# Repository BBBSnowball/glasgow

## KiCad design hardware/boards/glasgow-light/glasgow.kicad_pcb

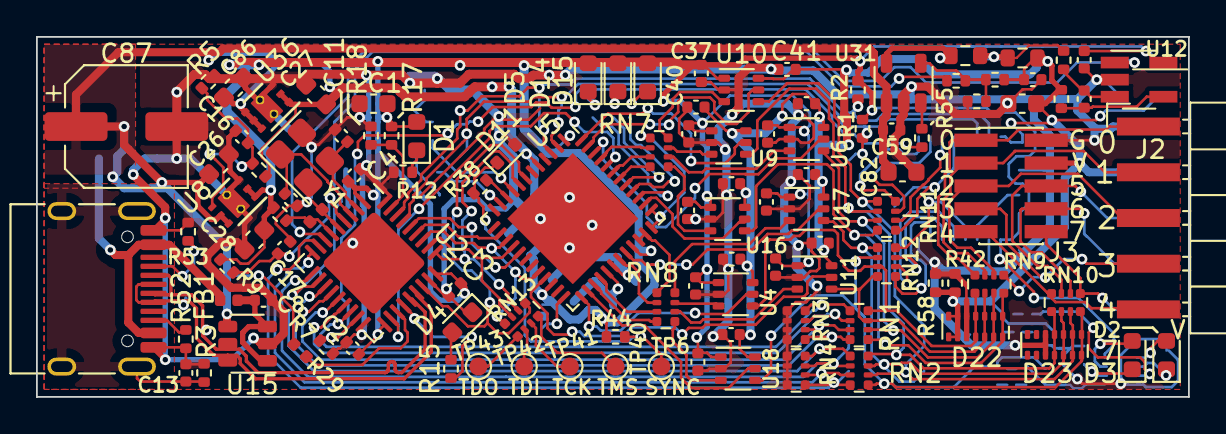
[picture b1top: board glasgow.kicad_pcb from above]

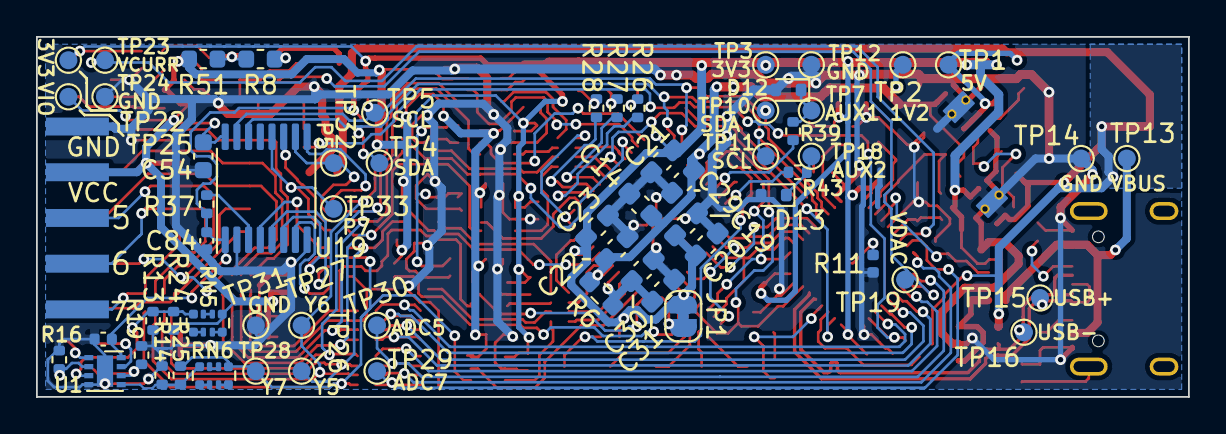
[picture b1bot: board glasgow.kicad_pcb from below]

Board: 2 copper layers, 64.0 x 20.0 mm, 173 parts (62 on the bottom side), 128 nets.

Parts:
C1, C26, C27, C28, C82, C83, C86: 4u7; C_0603_1608Metric
C2, C3, C4, C8, C13, C15, C16, C17, C32, C34, C35, C36, C37, C38, C39, C40, C41, C42, C43, C47, C48, C49, C50, C51, C52, C55, C57, C58, C59, C84: u1; C_0402_1005Metric
C11, C12: 9p; C_0402_1005Metric
C14, C19, C30: 4u7; C_0603_1608Metric_Pad1.08x0.95mm_HandSolder
C20, C21, C22, C23, C29, C31: u1; C_0603_1608Metric_Pad1.08x0.95mm_HandSolder
C54: u1; C_0603_1608Metric
C87: 150u; CP_Elec_6.3x5.9
D1: GRN; LED_0603_1608Metric
D2: GREEN; LED_0603_1608Metric
D3: YELLOW; LED_0603_1608Metric
D4, D5, D14, D15: YEL; LED_0603_1608Metric
D11, D12, D13: ESD5Z5.0T1G; D_SOD-523
D22, D23: SP3012-06UTG; UDFN-14_3.5x1.35mm_P0.5mm
FB1: 600R, 0.5A; L_0402_1005Metric
J1: USB_C_USB2.0; USB_C_Receptacle_HRO_TYPE-C-31-M-12
J2: IDC-Header_2x5_P2.54mm; PinHeader_2x05_P2.54mm_BoardEdge
J3: IDC-Header_2x5_P2.54mm; PinHeader_2x05_P1.27mm_Vertical_SMD
JP1: SolderJumper_2_Bridged; SolderJumper-2_P1.3mm_Bridged_RoundedPad1.0x1.5mm
R1, R2, R15, R42, R58: 2k2; R_0402_1005Metric
R3, R5, R18: 100k; R_0402_1005Metric
R4: 1k; R_0402_1005Metric
R6: 100; R_0603_1608Metric_Pad0.98x0.95mm_HandSolder
R7, R9, R37, R44, R55: 10k; R_0402_1005Metric
R8, R51: DNP; R_0603_1608Metric_DNP
R10, R11, R26, R27, R28, R29: 0; R_0402_1005Metric
R12: 20k; R_0402_1005Metric
R13, R14: 50k; R_0402_1005Metric
R16, R19: 270; R_0402_1005Metric
R17: DNP; R_0402_1005Metric
R24, R25: DNP/400k; R_0402_1005Metric
R30, R54: 4R7; R_0402_1005Metric
R33: 49k9; R_0402_1005Metric
R34: 59k; R_0402_1005Metric
R35: 24k3; R_0402_1005Metric
R38, R39, R43: 47R; R_0402_1005Metric
R49: 0R10; R_0603_1608Metric
R52, R53: 5k1; R_0402_1005Metric
R56: 0R68; R_0603_1608Metric
RN1, RN2, RN3, RN4, RN5, RN6: 100k; R_Array_Convex_4x0402
RN7, RN8, RN9, RN10, RN13: 33R; R_Array_Convex_4x0402
RN11, RN12: 10k; R_Array_Convex_4x0402
TP1: 5V; TestPoint_Pad_D1.0mm
TP2: 1V2; TestPoint_Pad_D1.0mm
TP3, TP22: 3V3; TestPoint_Pad_D1.0mm
TP4, TP10: SDA; TestPoint_Pad_D1.0mm
TP5, TP11: SCL; TestPoint_Pad_D1.0mm
TP6: SYNC; TestPoint_Pad_D1.0mm
TP7: AUX1; TestPoint_Pad_D1.0mm
TP12, TP24, TP31: GND; TestPoint_Pad_D1.0mm
TP13: VBUS; TestPoint_Pad_D1.0mm
TP14: USBGND; TestPoint_Pad_D1.0mm
TP15: USBDP; TestPoint_Pad_D1.0mm
TP16: USBDM; TestPoint_Pad_D1.0mm
TP18: AUX2; TestPoint_Pad_D1.0mm
TP19: VDAC; TestPoint_Pad_D1.0mm
TP23: VCURR; TestPoint_Pad_D1.0mm
TP25: VIO; TestPoint_Pad_D1.0mm
TP26: Y5; TestPoint_Pad_D1.0mm
TP27: Y6; TestPoint_Pad_D1.0mm
TP28: Y7; TestPoint_Pad_D1.0mm
TP29: ADC7; TestPoint_Pad_D1.0mm
TP30: ADC5; TestPoint_Pad_D1.0mm
TP32: P5; TestPoint_Pad_D1.0mm
TP33: P7; TestPoint_Pad_D1.0mm
TP40: TMS; TestPoint_Pad_D1.0mm
TP41: TCK; TestPoint_Pad_D1.0mm
TP42: TDI; TestPoint_Pad_D1.0mm
TP43: TDO; TestPoint_Pad_D1.0mm
U1: LM358_DFN; DFN-8-1EP_2x2mm_P0.5mm_EP1.05x1.75mm
U2: GD32VF103T; QFN-36-1EP_6x6mm_P0.5mm_EP4.1x4.1mm
U4, U6, U9, U10, U11, U16, U17, U18: SN74LVC1T45DCKR; SOT-363_SC-70-6
U5: ICE40UP5K-SG48ITR; QFN-48-1EP_7x7mm_P0.5mm_EP5.15x5.15mm
U8: TLV75533PDRVR; DFN-6-1EP_2x2mm_P0.65mm_EP1x1.6mm_ThermalVias
U12: INA180A2; SOT-23-5_HandSoldering
U15: TPD3S014; SOT-23-6
U19: PCA6408APW; TSSOP-16_4.4x5mm_P0.65mm
U31: TPS73101DBV; SOT-23-5
U36: TLV73312PQDRVR; DFN-6-1EP_2x2mm_P0.65mm_EP1x1.6mm_ThermalVias
Y1: 8M; Crystal_SMD_3225-4Pin_3.2x2.5mm

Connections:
+1V2: C14.1, C22.1, C27.1, C29.1, R4.1, R6.2, TP2.1, U5.5, U5.30, U36.1, U36.2
+3V3: C1.1, C2.1, C3.1, C4.1, C19.1, C20.1, C21.1, C23.1, C28.1, C32.1, C34.1, C35.1, C36.1, C37.1, C42.1, C43.1, C47.1, C48.1, C55.1, C84.1, D1.2, D5.2, D14.2, D15.2, JP1.1, R1.2, R2.2, R9.1, R10.2, R17.1, R37.2, R44.2, TP3.1, TP22.1, U1.8, U2.1, U2.19, U2.27, U4.1, U5.1, U5.22, U5.33, U6.1, U8.1, U8.2, U9.1, U10.1, U11.1, U12.5, U16.1, U17.1, U18.1, U19.1
+5V: C26.2, C59.1, C82.1, C86.2, C87.1, R29.1, TP1.1, U8.5, U8.6, U15.4, U31.1, U36.4, U36.5, U36.6
/AUX1: R39.2, U5.9
/AUX2: R43.2, U5.11
/BOOT0: R17.2, R18.1, U2.35
/CC1: J1.A5, R53.2
/CC2: J1.B5, R52.2
/CLKREF: U2.20, U5.44
/DA0: U4.5, U5.25
/DA1: U5.21, U11.5
/DA2: U5.46, U6.5
/DA3: U5.38, U16.5
/DA4: U5.48, U9.5
/DA5: U5.32, U17.5
/DA6: U5.47, U10.5
/DA7: U5.26, U18.5
/FPGA_DONE: RN13.1, U2.25, U5.7
/IO_Banks/AUX1~: D12.1, R39.1, TP7.1
/IO_Banks/AUX2~: D13.1, R43.1, TP18.1
/IO_Banks/IO_Buffer_A/P0: RN12.8, U19.4
/IO_Banks/IO_Buffer_A/P1: RN12.6, U19.5
/IO_Banks/IO_Buffer_A/P2: RN12.7, U19.6
/IO_Banks/IO_Buffer_A/P3: RN12.5, U19.7
/IO_Banks/IO_Buffer_A/P4: RN11.8, U19.9
/IO_Banks/IO_Buffer_A/P5: RN11.7, TP32.1, U19.10
/IO_Banks/IO_Buffer_A/P6: RN11.6, U19.11
/IO_Banks/IO_Buffer_A/P7: RN11.5, TP33.1, U19.12
/IO_Banks/IO_Buffer_A/VFB: R33.2, R34.1, R35.2, U31.4
/IO_Banks/IO_Buffer_A/VIO_EN: R55.1, U31.3
/IO_Banks/IO_Buffer_A/X0: RN7.8, U10.3
/IO_Banks/IO_Buffer_A/Y0: D22.4, D22.11, RN1.4, RN9.1, RN12.3, U4.4
/IO_Banks/IO_Buffer_A/Y1: D22.3, D22.12, RN1.3, RN9.2, RN12.4, U11.4
/IO_Banks/IO_Buffer_A/Y2: D22.2, D22.13, RN1.2, RN9.3, RN11.3, U6.4
/IO_Banks/IO_Buffer_A/Y3: D22.1, D22.14, RN1.1, RN9.4, RN11.4, U16.4
/IO_Banks/IO_Buffer_A/Y4: D23.4, D23.11, RN2.4, RN10.1, RN11.2, U9.4
/IO_Banks/IO_Buffer_A/Y5: D23.3, D23.12, RN2.3, RN10.2, RN12.1, TP26.1, U17.4
/IO_Banks/IO_Buffer_A/Y6: D23.2, D23.13, RN2.2, RN10.3, RN11.1, TP27.1, U10.4
/IO_Banks/IO_Buffer_A/Y7: D23.1, D23.14, R25.2, RN2.1, RN6.5, RN10.4, RN12.2, TP28.1, U18.4
/IO_Banks/IO_Buffer_A/Z0: J2.1, J3.1, RN9.8
/IO_Banks/IO_Buffer_A/Z1: J2.3, J3.3, RN9.7
/IO_Banks/IO_Buffer_A/Z2: J2.5, J3.5, RN9.6
/IO_Banks/IO_Buffer_A/Z3: J2.7, J3.7, RN9.5
/IO_Banks/IO_Buffer_A/Z4: J2.9, J3.9, RN10.8
/IO_Banks/IO_Buffer_A/Z5: J2.6, J3.6, RN10.7
/IO_Banks/IO_Buffer_A/Z6: J2.8, J3.8, RN10.6
/IO_Banks/IO_Buffer_A/Z7: J2.10, J3.10, RN10.5
/IO_Banks/VIOA: C38.1, C39.1, C40.1, C41.1, C49.1, C50.1, C51.1, C52.1, C54.1, C57.1, C83.1, D22.6, D22.7, D22.8, D22.9, J2.4, J3.4, R24.2, R34.2, R42.2, R49.2, R51.2, R54.1, R58.2, RN5.5, TP25.1, U4.6, U6.6, U9.6, U10.6, U11.6, U16.6, U17.6, U18.6, U19.16
/IO_Banks/~SYNC: D11.1, R38.1, R44.1, TP6.1
/LED0: R26.2, U5.39
/LED1: R27.2, U5.41
/LED2: R28.2, U5.40
/LED_ACT: R15.1, U2.22
/NRST: C17.1, R9.2, U2.4
/QA0: RN8.2, U5.31
/QA1: RN8.3, U5.28
/QA2: RN7.3, U5.43
/QA3: RN7.4, U5.42
/QA4: RN7.2, U5.45
/QA5: RN8.1, U5.34, U5.35
/QA6: RN7.1, U5.36, U5.37
/QA7: RN8.4, U5.27
/SCL: R1.1, TP4.1, TP11.1, U2.33, U5.2, U19.14
/SDA: R2.1, TP5.1, TP10.1, U2.34, U5.3, U19.15
/SHLD: C13.1, J1.S1, R3.1
/TCK: RN13.7, TP41.1
/TDI: RN13.6, TP42.1
/TDO: RN13.5, TP43.1
/TMS: RN13.8, TP40.1
/USB_N: J1.A7, J1.B7, TP16.1, U2.23, U15.5
/USB_P: J1.A6, J1.B6, TP15.1, U2.24, U15.6
/VCCPLL: C30.1, C31.1, R6.1, U5.29
/VDDA: C15.1, R10.1, U2.6
/VUSB: C8.1, FB1.2, U15.1, U15.3
/XTALIN: C12.1, U2.3, Y1.1
/XTALOUT: C11.1, U2.2, Y1.3
/xVBUS: FB1.1, J1.A4, J1.A9, J1.B4, J1.B9, TP13.1
/~FPGA_RESET: RN13.2, U2.28, U5.8
/~SYNC_INT: R38.2, U5.10
ADC0: RN1.5, RN3.4, U2.16
ADC1: RN1.6, RN3.3, U2.15
ADC2: RN1.7, RN3.2, U2.14
ADC3: RN1.8, RN3.1, U2.13
ADC4: RN2.5, RN4.4, U2.12
ADC5: RN2.6, RN4.3, TP30.1, U2.10
ADC6: RN2.7, RN4.2, U2.9
ADC7: RN2.8, RN4.1, TP29.1, U2.8
FPGA_CS: RN13.3, U2.29, U5.16
FPGA_MISO: U2.31, U5.14
FPGA_MOSI: U2.32, U5.17
FPGA_SCK: RN13.4, U2.30, U5.15, U5.20
GND: C1.2, C2.2, C3.2, C4.2, C8.2, C11.2, C12.2, C13.2, C14.2, C15.2, C16.2, C17.2, C19.2, C20.2, C21.2, C22.2, C23.2, C26.1, C27.2, C28.2, C29.2, C30.2, C31.2, C32.2, C34.2, C35.2, C36.2, C37.2, C38.2, C39.2, C40.2, C41.2, C42.2, C43.2, C47.2, C48.2, C49.2, C50.2, C51.2, C52.2, C54.2, C55.2, C57.2, C59.2, C82.2, C83.2, C84.2, C86.1, C87.2, D4.1, D11.2, D12.2, D13.2, D22.5, D22.10, D23.5, D23.10, J1.A1, J1.A12, J1.B1, J1.B12, J2.2, J3.2, R3.2, R5.2, R7.1, R11.2, R12.2, R13.2, R14.2, R16.2, R18.2, R19.2, R35.1, R42.1, R52.1, R53.1, R58.1, RN3.5, RN3.6, RN3.7, RN3.8, RN4.5, RN4.6, RN4.7, RN4.8, TP12.1, TP14.1, TP24.1, TP31.1, U1.4, U1.9, U2.5, U2.18, U2.26, U2.36, U4.2, U5.49, U6.2, U8.3, U8.7, U9.2, U10.2, U11.2, U12.2, U15.2, U16.2, U17.2, U18.2, U19.2, U19.8, U31.2, U36.3, U36.7, Y1.2, Y1.4
unnamed: C16.1, R4.2, R5.1, U8.4
unnamed: C58.1, R54.2, U12.4
unnamed: C58.2, R30.2, U12.3
unnamed: D1.1, R12.1
unnamed: D2.1, R16.1, U1.2
unnamed: D2.2, U1.1
unnamed: D3.1, R19.1, U1.6
unnamed: D3.2, U1.7
unnamed: D4.2, R15.2
unnamed: D5.1, R26.1
unnamed: D14.1, R27.1
unnamed: D15.1, R28.1
unnamed: JP1.2, U5.24
unnamed: R11.1, U2.37
unnamed: R13.1, R24.1, RN5.8, U1.3
unnamed: R14.1, R25.1, RN6.8, U1.5
unnamed: R29.2, U2.21
unnamed: R8.2, R30.1, R49.1, R51.1, R56.2
unnamed: R37.1, U19.3
unnamed: R8.1, R56.1, U31.5
unnamed: RN5.1, RN5.2
unnamed: RN5.3, RN5.4
unnamed: RN5.6, RN5.7
unnamed: RN6.1, RN6.2
unnamed: RN6.3, RN6.4
unnamed: RN6.6, RN6.7
unnamed: RN7.5, U16.3
unnamed: RN7.6, U6.3
unnamed: RN7.7, U9.3
unnamed: RN8.5, U18.3
unnamed: RN8.6, U11.3
unnamed: RN8.7, U4.3
unnamed: RN8.8, U17.3
VIO_CURRENT: TP23.1, U2.7, U12.1
VIO_DAC: R33.1, TP19.1, U2.11
VIO_ENA: R7.2, R55.2, U2.17

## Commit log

2021-01-04 start with glasgow-light
2021-01-04 swap some pins
2021-01-06 place&route the buffers
2021-01-06 fix routing problems near the buffers
2021-01-06 route resistor arrays between FPGA and buffers
2021-01-06 increase width of supply lines
2021-01-06 add some test points
2021-01-06 add LEDs for VIO and Y7
2021-01-06 add alternative resistors
    We might not want to place any resistor arrays on the bottom side
    because we will most likely hand-solder it.
2021-01-08 start routing FPGA
2021-01-08 right side of FPGA routed
2021-01-09 continue routing around FPGA
2021-01-09 swap some of the DAx pins, again
2021-02-24 something
2021-02-24 add pinout for GD32VF103TBU6 (QFN36)
2021-02-24 replace symlinks
2021-02-25 open project on another host
2021-02-25 add GD32VF103T in QFN36 package
2021-02-27 rotate GD32 -> routing is *much* easier
2021-02-27 replace SYNC and AUX connectors by test points
2021-02-27 most components are placed
2021-02-28 optimize
2021-02-28 make the board a bit smaller
2021-02-28 make board another bit smaller -> outer size is metric
2021-02-28 add optional connection for exposed pad of GD32VF
    The datasheet doesn't say whether we should connect it to GND.
2021-02-28 optimize location of test points
2021-02-28 start optimizing silk
2021-02-28 add silk for connectors
2021-03-02 add solder jumper for VPP_2V5
2021-03-02 optimize a few wires
